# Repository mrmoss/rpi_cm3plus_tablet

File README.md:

# RPi CM3+ Tablet
Work in progress board for a tablet based on the RPi CM3+ module.

MVP is to make a small daughter board to plug into the official RPi 7in touchscreen.

Long-term goal is to make a complete swapout for the control board on the official RPi 7in touchscreen.

Both of these will hopefully have a built in 1S lithium charger with a 5V boost converter, speaker, WiFi, and bluetooth, and headphone jack.

Current design simply has the RPi CM3+ footprint with minimally connected power (without a 5V input to VBAT at the moment) and DSI port for the 7in display.

Will hopefully continue development when evaluation board comes in to do some hands-on testing before continuing with development.

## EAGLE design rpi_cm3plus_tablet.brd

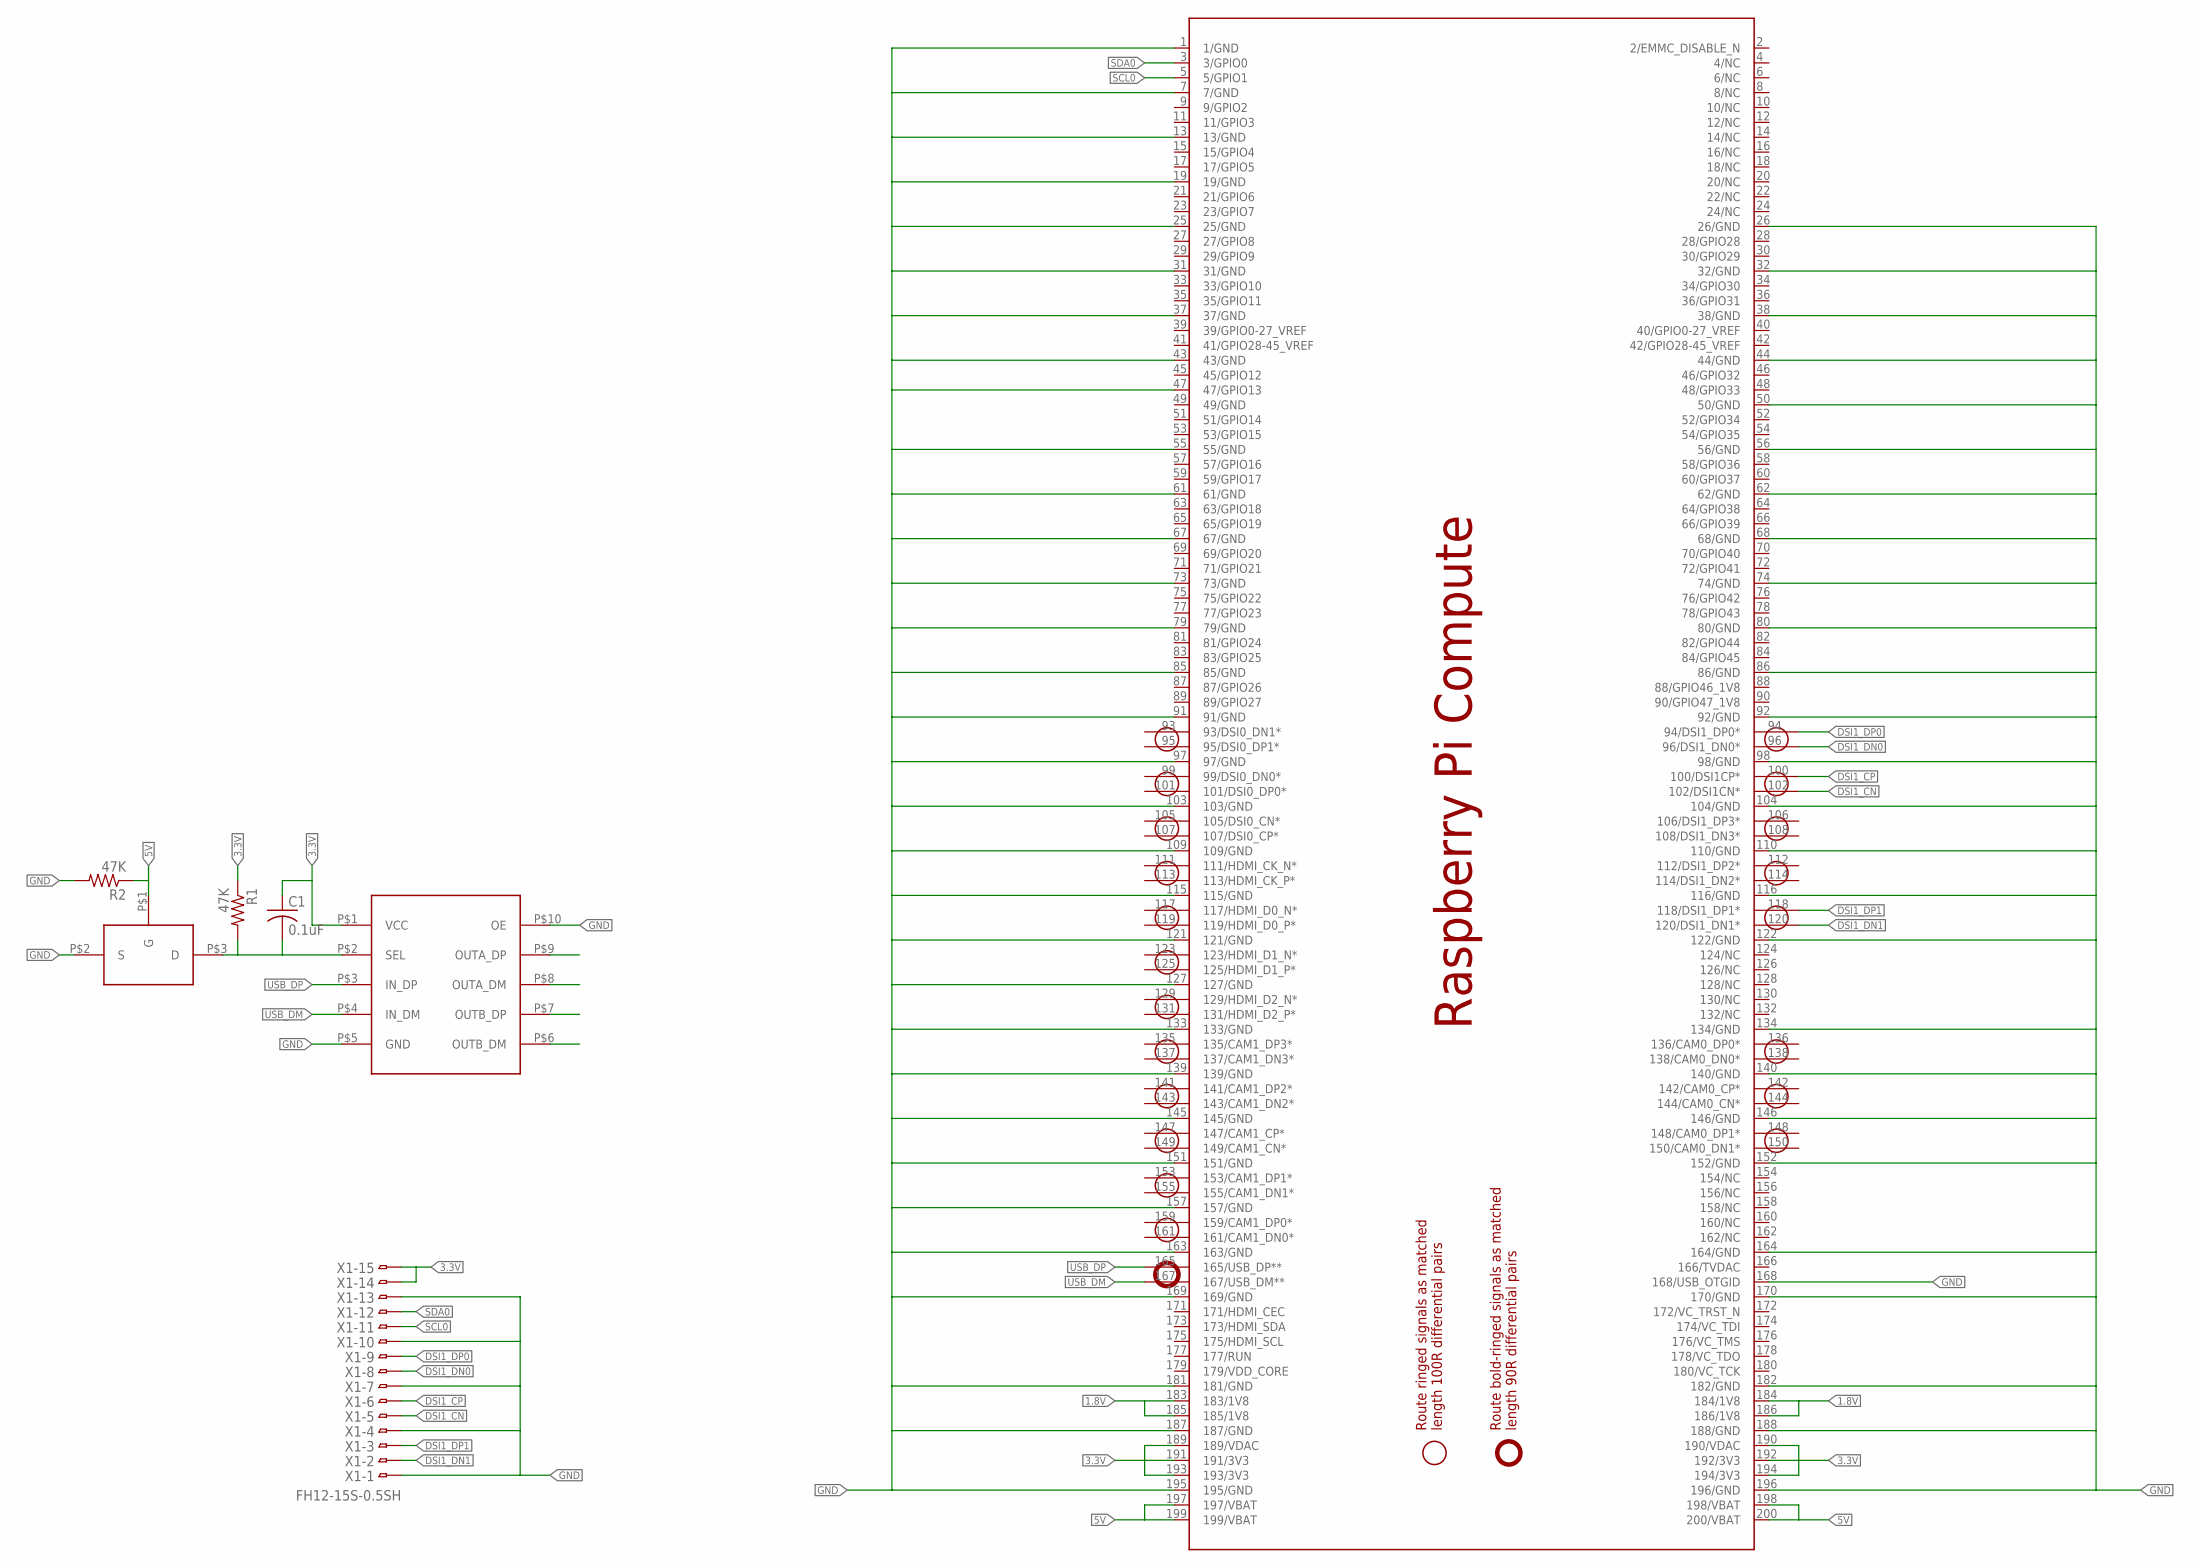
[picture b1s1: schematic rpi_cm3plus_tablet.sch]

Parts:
C1: 0.1uF; C0603K
PCB1: RPI_COMPUTE
R1, R2: 47K; R0603
U$1: FSUSB42MUX; MSOP-10
U$2: BSS138N; SOT-23
X1: FH12-15S-0.5SH

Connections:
1.8V: PCB1.183 (183/1V8), PCB1.184 (184/1V8), PCB1.185 (185/1V8), PCB1.186 (186/1V8)
3.3V: C1.1, PCB1.189 (189/VDAC), PCB1.190 (190/VDAC), PCB1.191 (191/3V3), PCB1.192 (192/3V3), PCB1.193 (193/3V3), PCB1.194 (194/3V3), R1.1, U$1.P$1 (VCC), X1.14, X1.15
5V: PCB1.197 (197/VBAT), PCB1.198 (198/VBAT), PCB1.199 (199/VBAT), PCB1.200 (200/VBAT), R2.1, U$2.P$1 (G)
DSI1_CN: PCB1.102 (102/DSI1CN*), X1.5
DSI1_CP: PCB1.100 (100/DSI1CP*), X1.6
DSI1_DN0: PCB1.96 (96/DSI1_DN0*), X1.8
DSI1_DN1: PCB1.120 (120/DSI1_DN1*), X1.2
DSI1_DP0: PCB1.94 (94/DSI1_DP0*), X1.9
DSI1_DP1: PCB1.118 (118/DSI1_DP1*), X1.3
GND: PCB1.1 (1/GND), PCB1.7 (7/GND), PCB1.13 (13/GND), PCB1.19 (19/GND), PCB1.25 (25/GND), PCB1.26 (26/GND), PCB1.31 (31/GND), PCB1.32 (32/GND), PCB1.37 (37/GND), PCB1.38 (38/GND), PCB1.43 (43/GND), PCB1.44 (44/GND), PCB1.47 (47/GPIO13), PCB1.50 (50/GND), PCB1.55 (55/GND), PCB1.56 (56/GND), PCB1.61 (61/GND), PCB1.62 (62/GND), PCB1.67 (67/GND), PCB1.68 (68/GND), PCB1.73 (73/GND), PCB1.74 (74/GND), PCB1.79 (79/GND), PCB1.80 (80/GND), PCB1.85 (85/GND), PCB1.86 (86/GND), PCB1.91 (91/GND), PCB1.92 (92/GND), PCB1.97 (97/GND), PCB1.98 (98/GND), PCB1.103 (103/GND), PCB1.104 (104/GND), PCB1.109 (109/GND), PCB1.110 (110/GND), PCB1.115 (115/GND), PCB1.116 (116/GND), PCB1.121 (121/GND), PCB1.122 (122/GND), PCB1.127 (127/GND), PCB1.133 (133/GND), PCB1.134 (134/GND), PCB1.139 (139/GND), PCB1.140 (140/GND), PCB1.145 (145/GND), PCB1.146 (146/GND), PCB1.151 (151/GND), PCB1.152 (152/GND), PCB1.157 (157/GND), PCB1.163 (163/GND), PCB1.164 (164/GND), PCB1.168 (168/USB_OTGID), PCB1.169 (169/GND), PCB1.170 (170/GND), PCB1.181 (181/GND), PCB1.182 (182/GND), PCB1.187 (187/GND), PCB1.188 (188/GND), PCB1.195 (195/GND), PCB1.196 (196/GND), R2.2, U$1.P$5 (GND), U$1.P$10 (OE), U$2.P$2 (S), X1.1, X1.4, X1.7, X1.10, X1.13
unnamed: C1.2, R1.2, U$1.P$2 (SEL), U$2.P$3 (D)
SCL0: PCB1.5 (5/GPIO1), X1.11
SDA0: PCB1.3 (3/GPIO0), X1.12
USB_DM: PCB1.167 (167/USB_DM**), U$1.P$4 (IN_DM)
USB_DP: PCB1.165 (165/USB_DP**), U$1.P$3 (IN_DP)

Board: 2 copper layers, 7 parts (0 on the bottom side), 15 nets, no tracks yet.

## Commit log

2019-02-22 rename...
2019-02-26 removed tvdac (should be unused)
2019-02-27 Modified library to include some custom parts and added a basic usb circuit.
2019-02-27 further updates to schematic regarding custom library
2019-02-27 added datasheets and parts list (wip)
